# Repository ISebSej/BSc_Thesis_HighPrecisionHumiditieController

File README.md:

# BSc_Thesis_HighPrecisionHumidityController

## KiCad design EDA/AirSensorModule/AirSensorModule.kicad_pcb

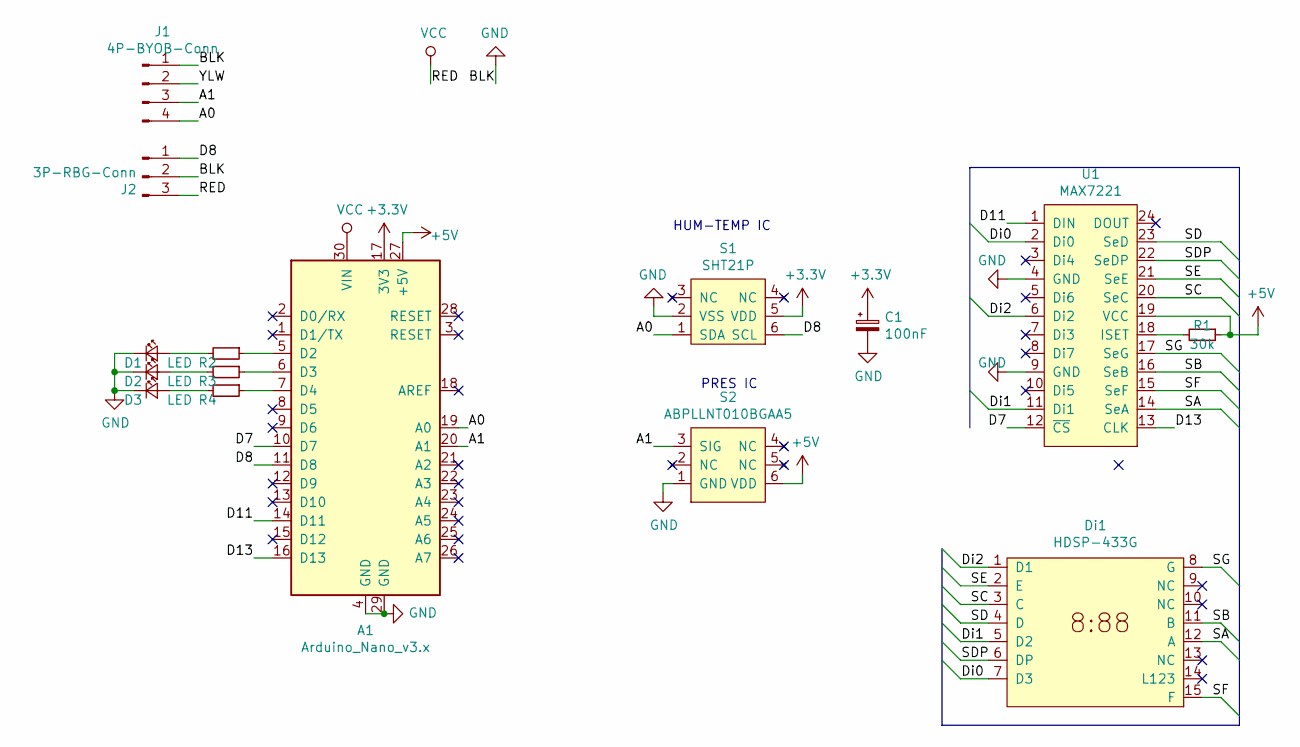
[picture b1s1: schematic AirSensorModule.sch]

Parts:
A1: Arduino_Nano_v3.x; Arduino_Nano
C1: 100nF; CP_Radial_Tantal_D7.0mm_P2.50mm
D1, D2, D3: LED; LED_0603_1608Metric
Di1: HDSP-433G
J1: 4P-BYOB-Conn; FanPinHeader_1x04_P2.54mm_Vertical
J2: 3P-RBG-Conn; FanPinHeader_1x03_P2.54mm_Vertical
R1: 30k; R_Axial_DIN0204_L3.6mm_D1.6mm_P5.08mm_Horizontal
R2, R3, R4: R_Axial_DIN0204_L3.6mm_D1.6mm_P5.08mm_Horizontal
S1: SHT21P; DFN-6-1EP_3x3mm_P1mm_EP1.5x2.4mm
S2: ABPLLNT010BGAA5; ABPxx - LeadlessSMT
U1: MAX7221; DIP-24_W7.62mm_LongPads

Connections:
+3V3: A1.17 (3V3), C1.1, S1.5 (VDD)
+5V: A1.27 (+5V), R1.1, S2.6 (VDD), U1.19 (VCC)
/A0: A1.19 (A0), J1.4, S1.1 (SDA)
/A1: A1.20 (A1), J1.3, S2.3 (SIG)
/D7: A1.10 (D7), U1.12 (~CS)
/D8: A1.11 (D8), J2.1, S1.6 (SCL)
/D11: A1.14 (D11), U1.1 (DIN)
/D13: A1.16 (D13), U1.13 (CLK)
/Di0: Di1.7 (D3), U1.2 (Di0)
/Di1: Di1.5 (D2), U1.11 (Di1)
/Di2: Di1.1 (D1), U1.6 (Di2)
/SA: Di1.12 (A), U1.14 (SeA)
/SB: Di1.11 (B), U1.16 (SeB)
/SC: Di1.3 (C), U1.20 (SeC)
/SD: Di1.4 (D), U1.23 (SeD)
/SDP: Di1.6 (DP), U1.22 (SeDP)
/SE: Di1.2 (E), U1.21 (SeE)
/SF: Di1.15 (F), U1.15 (SeF)
/SG: Di1.8 (G), U1.17 (SeG)
/YLW: J1.2
GND: A1.4 (GND), A1.29 (GND), C1.2, D1.1 (K), D2.1 (K), D3.1 (K), J1.1, J2.2, S1.2 (VSS), S1.7, S2.1 (GND), U1.4 (GND), U1.9 (GND)
unnamed: A1.5 (D2), R2.1
unnamed: A1.6 (D3), R3.1
unnamed: A1.7 (D4), R4.1
unnamed: D1.2 (A), R2.2
unnamed: D2.2 (A), R3.2
unnamed: D3.2 (A), R4.2
unnamed: R1.2, U1.18 (ISET)
VCC: A1.30 (VIN), J2.3

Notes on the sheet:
HUM-TEMP IC
PRES IC

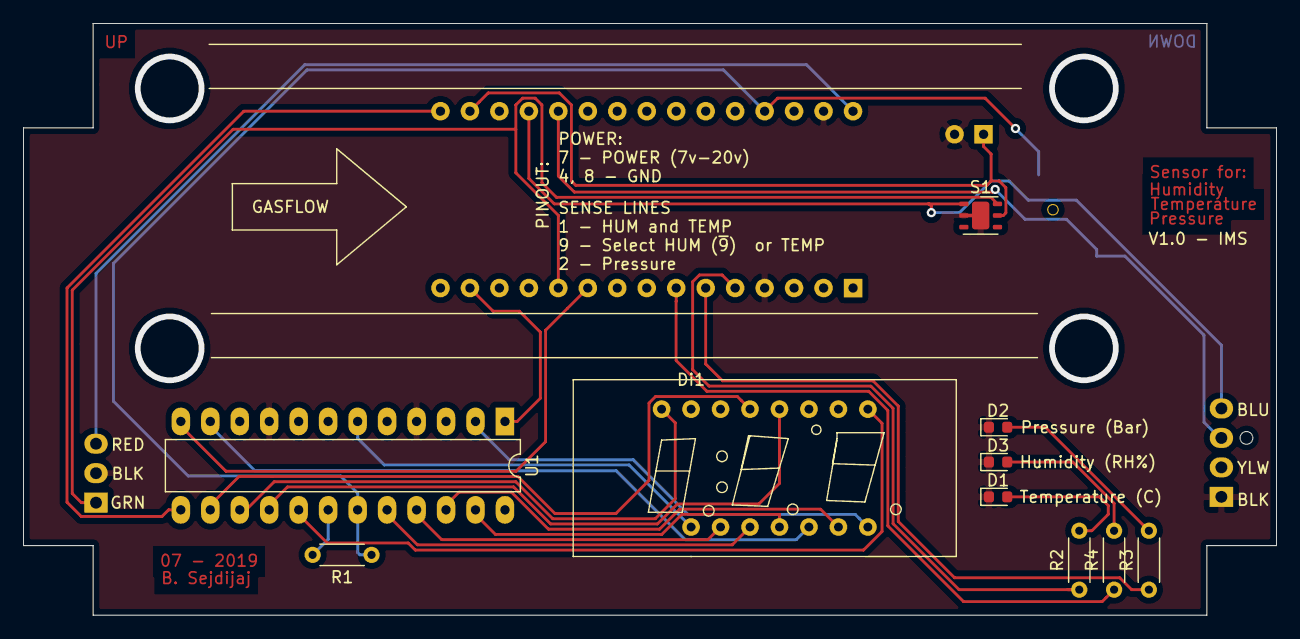
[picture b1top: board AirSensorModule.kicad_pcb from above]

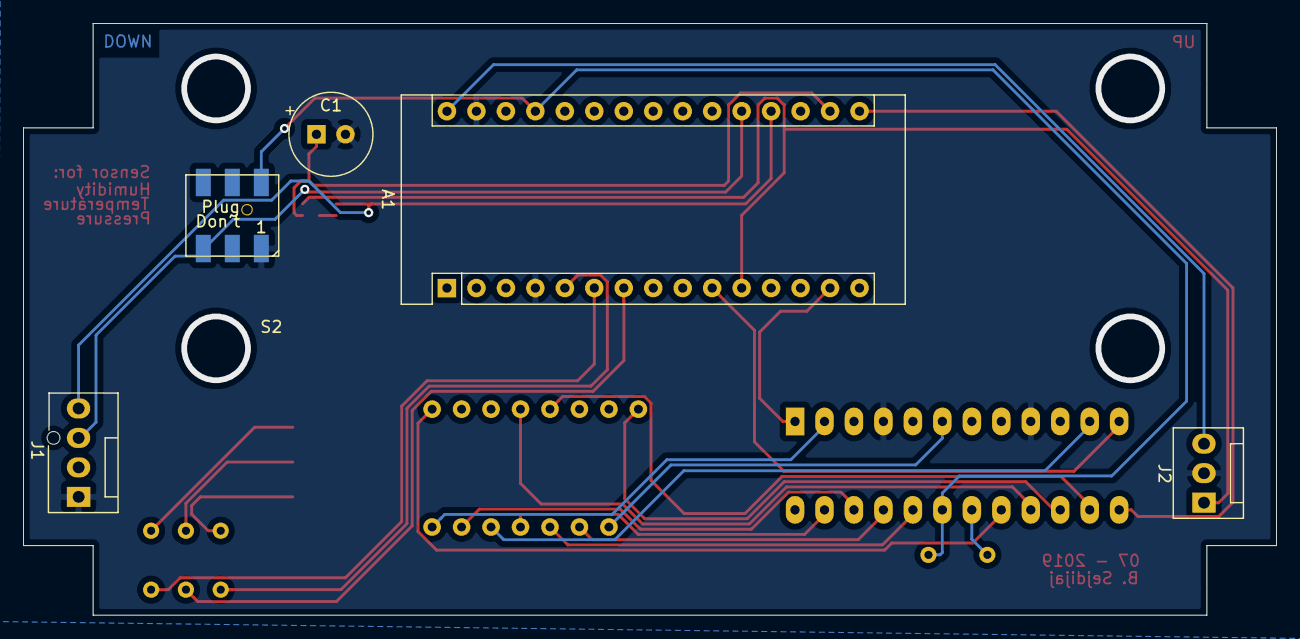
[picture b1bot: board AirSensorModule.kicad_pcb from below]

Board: 2 copper layers, 108.0 x 51.0 mm, 15 parts (5 on the bottom side), 28 nets.

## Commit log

2020-11-11 BES - initial commit
